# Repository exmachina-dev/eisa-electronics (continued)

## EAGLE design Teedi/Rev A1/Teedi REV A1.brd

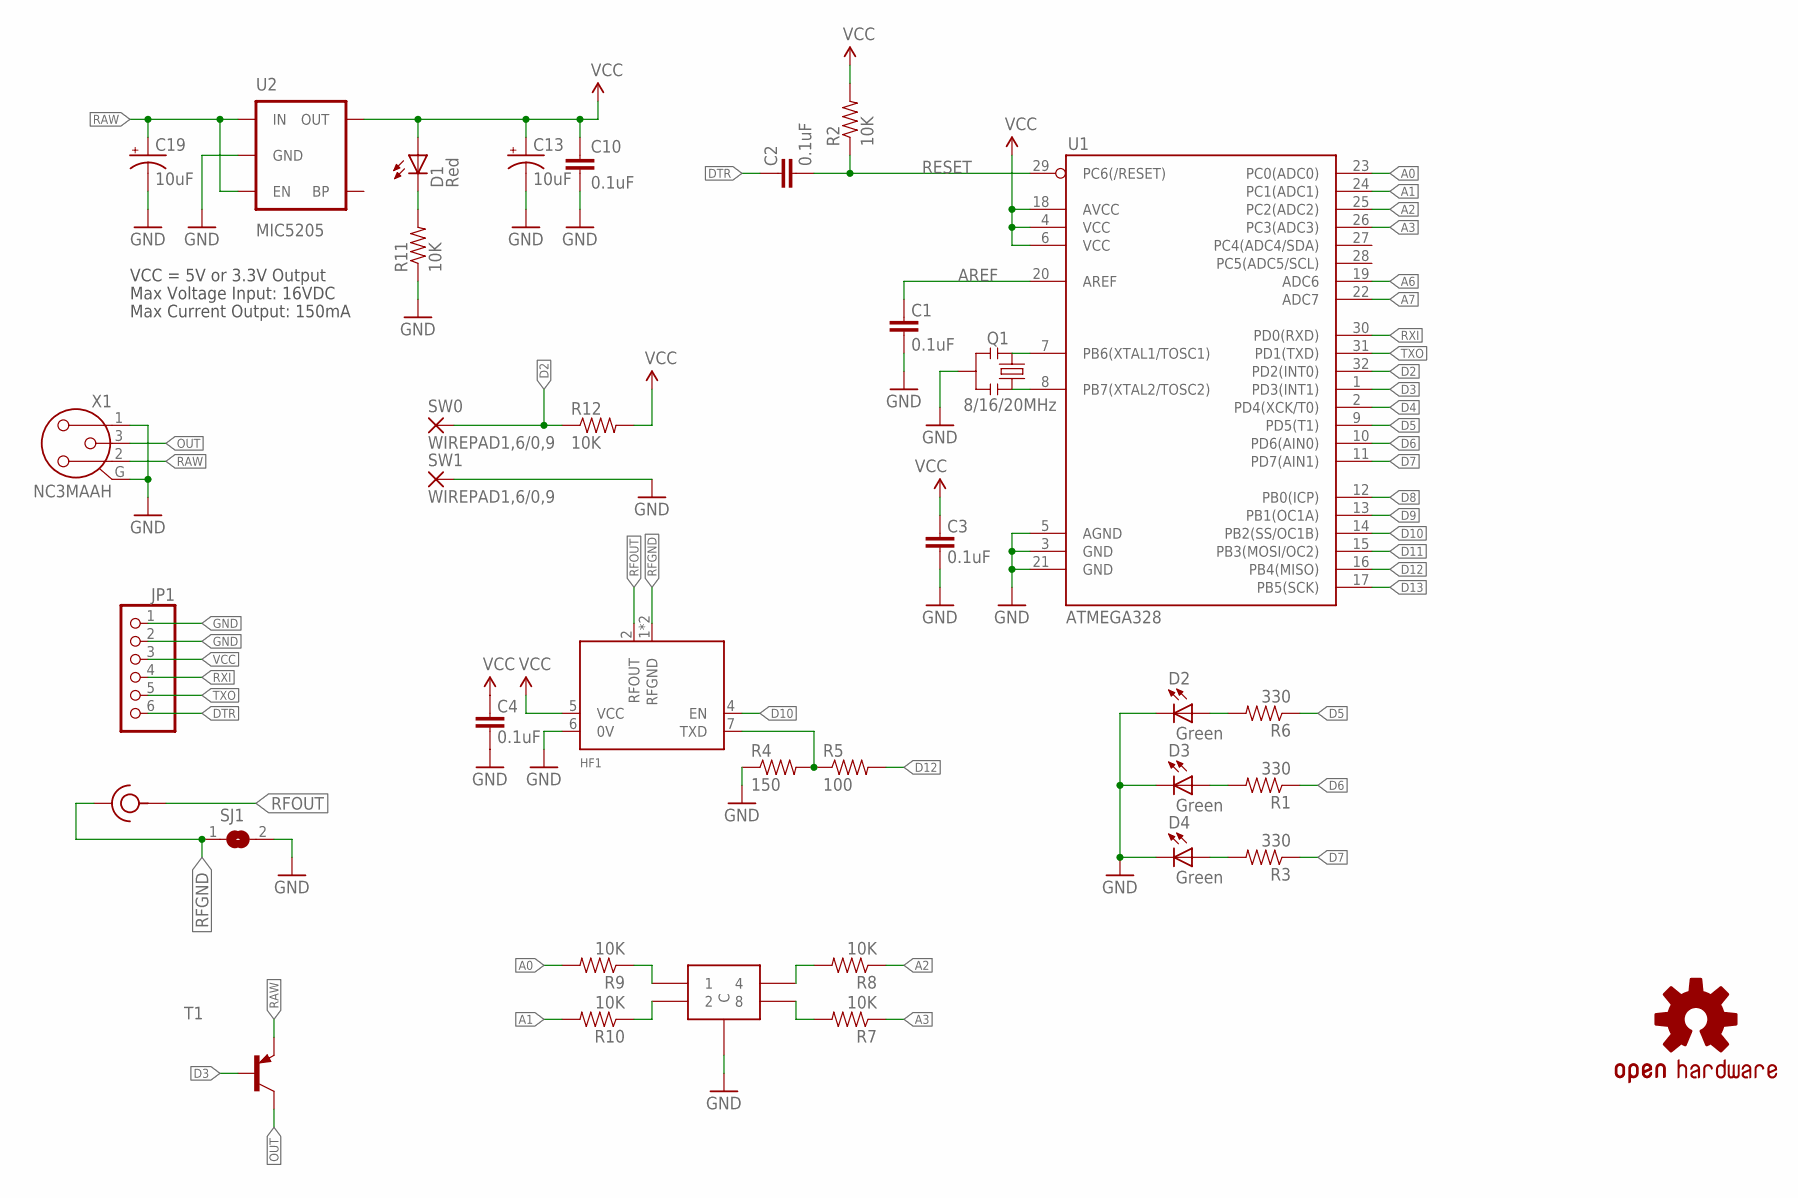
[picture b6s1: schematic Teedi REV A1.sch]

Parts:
C1, C2, C3, C4, C10: 0.1uF; 0603-CAP; MPN MC0603F104Z160CT
C13, C19: 10uF; EIA3216; MPN MCCTA106M006
D1: Red; 0603-LED-ALT1; MPN MCL-S290SRC
D2, D3, D4: Green; 0603-LED-ALT1; MPN 703-0109
HF1: TX2A-433-64; TX2A; MPN TX2A-433-64
JP1: PINHD-1X6; 1X06; MPN MC34751
Q1: 8/16/20MHz; RESONATOR-SMD-1:1; MPN CSTCE8M00G55Z-R0
R1, R3, R6: 330; 0603-RES; MPN MCWR06X3300FTL
R2, R7, R8, R9, R10, R11, R12: 10K; 0603-RES; MPN MCHP03W8F1002T5E
R4: 150; 0603-RES; MPN MCWR06X1500FTL
R5: 100; 0603-RES; MPN MCWR06X1000FTL
RF1: 132203; MPN 132203
SJ1: SJ
SW0, SW1: WIREPAD1,6/0,9; 1,6/0,9
T1: -PNP-SOT23-BCE; SOT23-BCE; MPN BC807-25
U1: ATMEGA328; TQFP32-08; MPN ATMEGA328-AUR
U2: MIC5205; SOT23-5; MPN MIC5205-3.0YM5 TR
U$3: OSHW-LOGOS; OSHW-LOGO-S
U$5: PT65-101-L508; MPN PT65-101-L508
X1: NC3MAAH; NC3MAH; MPN NC3MAAH

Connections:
A0: R9.2, U1.23 (PC0(ADC0))
A1: R10.2, U1.24 (PC1(ADC1))
A2: R8.1, U1.25 (PC2(ADC2))
A3: R7.1, U1.26 (PC3(ADC3))
A6: U1.19 (ADC6)
A7: U1.22 (ADC7)
AREF: C1.2, U1.20 (AREF)
D2: R12.1, SW0.1, U1.32 (PD2(INT0))
D3: T1.B, U1.1 (PD3(INT1))
D4: U1.2 (PD4(XCK/T0))
D5: R6.1, U1.9 (PD5(T1))
D6: R1.1, U1.10 (PD6(AIN0))
D7: R3.1, U1.11 (PD7(AIN1))
D8: U1.12 (PB0(ICP))
D9: U1.13 (PB1(OC1A))
D10: HF1.4 (EN), U1.14 (PB2(SS/OC1B))
D11: U1.15 (PB3(MOSI/OC2))
D12: R5.2, U1.16 (PB4(MISO))
D13: U1.17 (PB5(SCK))
DTR: C2.2, JP1.6
GND: C1.1, C3.1, C4.1, C10.2, C13.C (-), C19.C (-), D2.C, D3.C, D4.C, HF1.6 (0V), JP1.1, JP1.2, Q1.2, R4.1, R11.1, SJ1.2, SW1.1, U1.3 (GND), U1.5 (AGND), U1.21 (GND), U2.2 (GND), U$5.C1 (C), U$5.C2 (C), X1.1, X1.G
unnamed: Q1.3, U1.8 (PB7(XTAL2/TOSC2))
unnamed: Q1.1, U1.7 (PB6(XTAL1/TOSC1))
unnamed: D3.A, R1.2
unnamed: D1.C, R11.2
unnamed: D4.A, R3.2
unnamed: HF1.7 (TXD), R4.2, R5.1
unnamed: D2.A, R6.2
unnamed: R9.1, U$5.1
unnamed: R10.1, U$5.2
unnamed: R8.2, U$5.4
unnamed: R7.2, U$5.8
OUT: T1.C, X1.3
RAW: C19.A (+), T1.E, U2.1 (IN), U2.3 (EN), X1.2
RESET: C2.1, R2.1, U1.29 (PC6(/RESET))
RFGND: HF1.1 (RFGND), HF1.3 (RFGND), RF1.G1 (GND), RF1.G2 (GND), RF1.G3 (GND), RF1.G4 (GND), SJ1.1
RFOUT: HF1.2 (RFOUT), RF1.P (RF)
RXI: JP1.4, U1.30 (PD0(RXD))
TXO: JP1.5, U1.31 (PD1(TXD))
VCC: C3.2, C4.2, C10.1, C13.A (+), D1.A, HF1.5 (VCC), JP1.3, R2.2, R12.2, U1.4 (VCC), U1.6 (VCC), U1.18 (AVCC), U2.5 (OUT)

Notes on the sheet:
Max Voltage Input: 16VDC
Max Current Output: 150mA
VCC = 5V or 3.3V Output

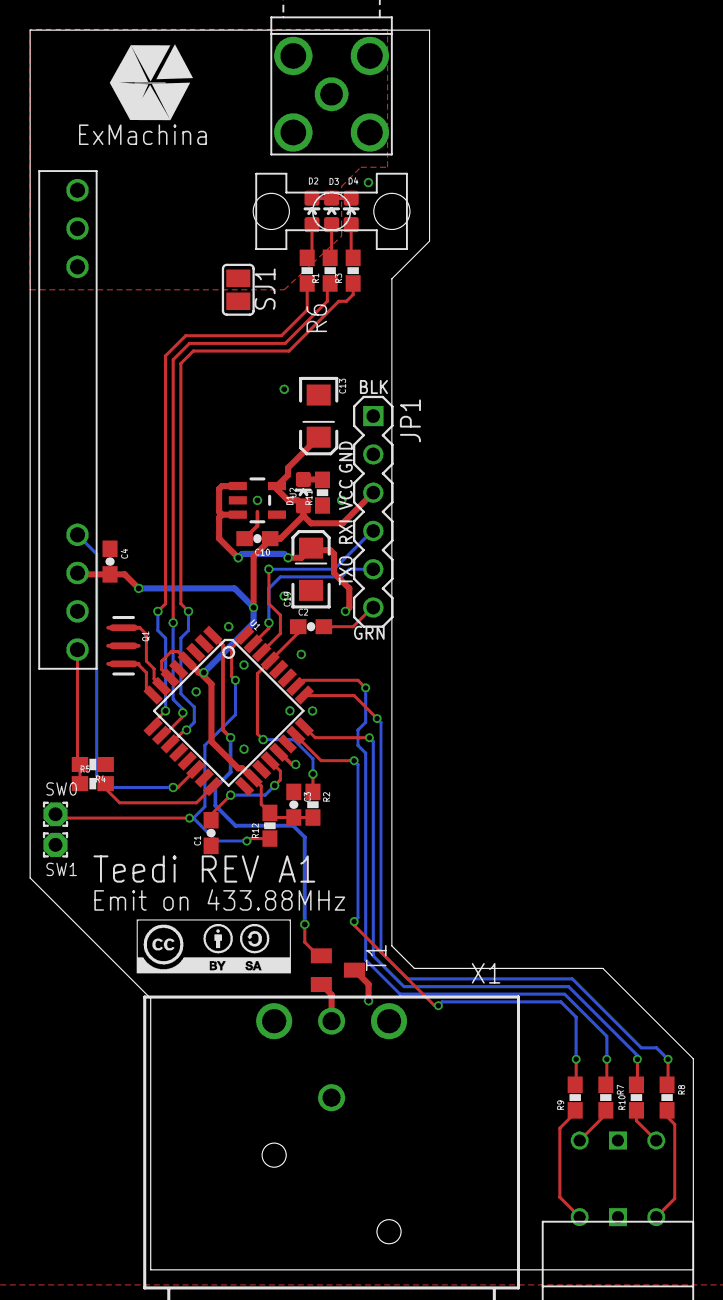
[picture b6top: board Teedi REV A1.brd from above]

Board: 2 copper layers, 44.0 x 82.2 mm, 39 parts (1 on the bottom side), 33 nets.

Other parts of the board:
U$4: CC-BY-SA
U$7: EXM-LOGO
U$8: 1275.100
